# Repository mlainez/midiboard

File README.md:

# MIDI IN/OUT 3V3/5V

A small MIDI interface board: opto-isolated MIDI IN, buffered MIDI OUT, optional hard THRU,
a 3V3/5V slide switch, and on-board footprints for two right-angle DIN-5 jacks.

Board: 46 x 39 mm, 2 layers, all SMD parts on top, 2x M3 mounting holes.

## Ordering at JLCPCB

Everything to upload is in `jlcpcb/`:

| File | Where |
|---|---|
| `midiboard-gerbers.zip` | PCB order: "Add gerber file" |
| `midiboard-BOM.csv` | PCB Assembly step: BOM |
| `midiboard-CPL.csv` | PCB Assembly step: CPL / pick & place |

1. Upload the gerber zip. Defaults are fine (2 layers, 1.6 mm, any colour/finish).
   For "Mark on PCB" choose **Remove Mark** (there is no order-number placeholder on the board).
2. Enable **PCB Assembly**, Economic, **Top side**.
3. Upload BOM and CPL. All 13 placed parts should match automatically:

   | Ref | Value | Package | LCSC | Type |
   |---|---|---|---|---|
   | U1 | H11L1SM optocoupler (onsemi) | SMD DIP-6 | C899473 | extended |
   | U2 | 74LVC1G17W5-7 Schmitt buffer | SOT-23-5 | C151394 | extended |
   | D1 | 1N4148W | SOD-123 | C81598 | basic |
   | SW1 | C&K JS202011JCQN DPDT slide switch | SMD | C221665 | extended |
   | R1, R4, R5 | 220 R | 0603 | C22962 | basic |
   | R2 | 470 R | 0603 | C23179 | basic |
   | R3 | 10 k | 0603 | C25804 | basic |
   | R6 | 33 R | 0805 | C17634 | basic |
   | R7 | 10 R | 0805 | C17415 | basic |
   | C1, C2 | 100 nF X7R | 0603 | C14663 | basic |

4. In the placement preview, check the pin-1 dots: U1 pin 1 is top-left (towards R1/D1), U2 pin 1 is
   top-left (silkscreen triangle). The CPL already applies the KiCad-to-JLCPCB rotation offsets
   (-90 deg for SOT-23-5 and SMD DIP-6).

### Hand-soldered (not in the JLCPCB BOM)

| Ref | Part | Note |
|---|---|---|
| J1, J2 | DIN-5 female, right angle, PCB mount: Legion/Haoyu **DIN-504**, LCSC **C23689428** | Any CUI SDS-50J-footprint jack fits |
| J3 | 1x4 pin header 2.54 mm | MCU side |
| J4 | 1x5 pin header 2.54 mm | Only if you use panel-mount jacks instead of J1/J2 |
| JP1 | 1x2 pin header 2.54 mm + jumper cap | HARD THRU selector |

The DIN jacks can also be added to the JLCPCB order as through-hole assembly if you prefer.

## Pins

**J3 - MCU** (3.3 V or 5 V logic, set SW1 to match)

| Pin | Name | Connect to |
|---|---|---|
| 1 | TX | MCU UART TX (31250 baud) |
| 2 | RX | MCU UART RX |
| 3 | GND | GND |
| 4 | VCC | 3.3 V or 5 V supply, same as the MCU logic level |

**J4 - panel jacks**: `i4`/`i5` to MIDI IN pins 4/5, `o5`/`o2`/`o4` to MIDI OUT pins 5/2/4.
These are wired in parallel with the on-board J1/J2 footprints.

**SW1 3V3 / 5V**: slide towards the jacks (`3V3`) for a 3.3 V MCU, towards the headers (`5V`) for a 5 V MCU.
It only sets the MIDI OUT drive; RX simply swings to VCC. A wrong setting is not harmful: 5 V on the 3V3
setting pushes ~15 mA into the receiver, 3.3 V on the 5V setting gives ~3 mA, which some receivers may not
detect.

**JP1 HARD THRU** (2-pin header, open by default): fit a 2.54 mm jumper cap to echo MIDI IN straight to the OUT jack.
When bridged, leave J3 TX unconnected.

## Circuit notes

- MIDI IN: 220 R + 1N4148W reverse protection into an H11L1 (rated 3-16 V), open-collector output pulled up
  to VCC by 470 R. Accepts 3.3 V and 5 V senders (current loop, ~5-8 mA). IN jack pin 2 is left unconnected and there is no ground copper on the IN side, so the
  input stays galvanically isolated as the MIDI spec requires.
- MIDI OUT: 74LVC1G17 buffer (1.65-5.5 V). 5V position: 220 R from VCC to pin 4 and 220 R in series with
  pin 5 (MIDI 1.0). 3V3 position: SW1 adds 33 R and 10 R in parallel, giving 28.7 R and 9.6 R (CA-033 asks
  for 33 R / 10 R; 33 R is the nearest JLCPCB basic part, ~7 mA instead of ~6.7 mA).
  10 k pull-up on TX keeps the output idle when TX is not driven.

## Verification

`build.sh` runs all of these and stops on failure:

- KiCad ERC on the schematic (0 errors).
- `scripts/check_netlist.py`: the schematic netlist matches `scripts/design.py`.
- KiCad DRC with schematic parity (0 unconnected, 0 parity issues, no clearance errors).
- `scripts/check_gerbers.py`: rasterizes the copper gerbers, joins layers through the drill file's plated
  holes, and derives connectivity from copper alone, then compares it with `design.py` (opens, shorts and
  NC pads). Mutating the expected design makes it fail, so it does detect wiring errors.

Checked by hand against datasheets: H11L1 pinout and inverting output (onsemi), 74LVC1G17 SOT25 pinout
(Diodes Inc), JS202011 contact positions (C&K: slider towards pin 1 closes 1-2 and 4-5), DIN-504 PCB layout
(Legion and Haoyu drawings agree), and the JLCPCB/EasyEDA footprints of C899473, C151394, C81598 and C221665
for the CPL rotations and diode polarity.

`midiboard.kicad_dru` lets through-hole pads have a single thermal spoke per layer: they are plated through
both ground pours, so the connection is solid either way.

## Sources

KiCad project: `midiboard.kicad_pro` / `.kicad_sch` / `.kicad_pcb`, project footprint in `lib/midiboard.pretty`.
`jlcpcb/midiboard-schematic.pdf` is a printable schematic.

Everything is generated from `scripts/design.py` (parts, LCSC numbers, nets):

```
FREEROUTING_JAR=/path/to/freerouting-2.1.0.jar ./build.sh
```

`build.sh` generates the schematic, runs ERC, checks the schematic netlist against `design.py`, places the
board, autoroutes it with Freerouting (headless), adds the ground pours, runs DRC with schematic parity and
writes the JLCPCB files, then checks the gerber copper. It needs KiCad 7 `pcbnew` Python, `kiutils`, numpy,
scipy, pillow, gerbv, Java 21 and a KiCad >= 8 `kicad-cli` (defaults to the KiCad Flatpak).

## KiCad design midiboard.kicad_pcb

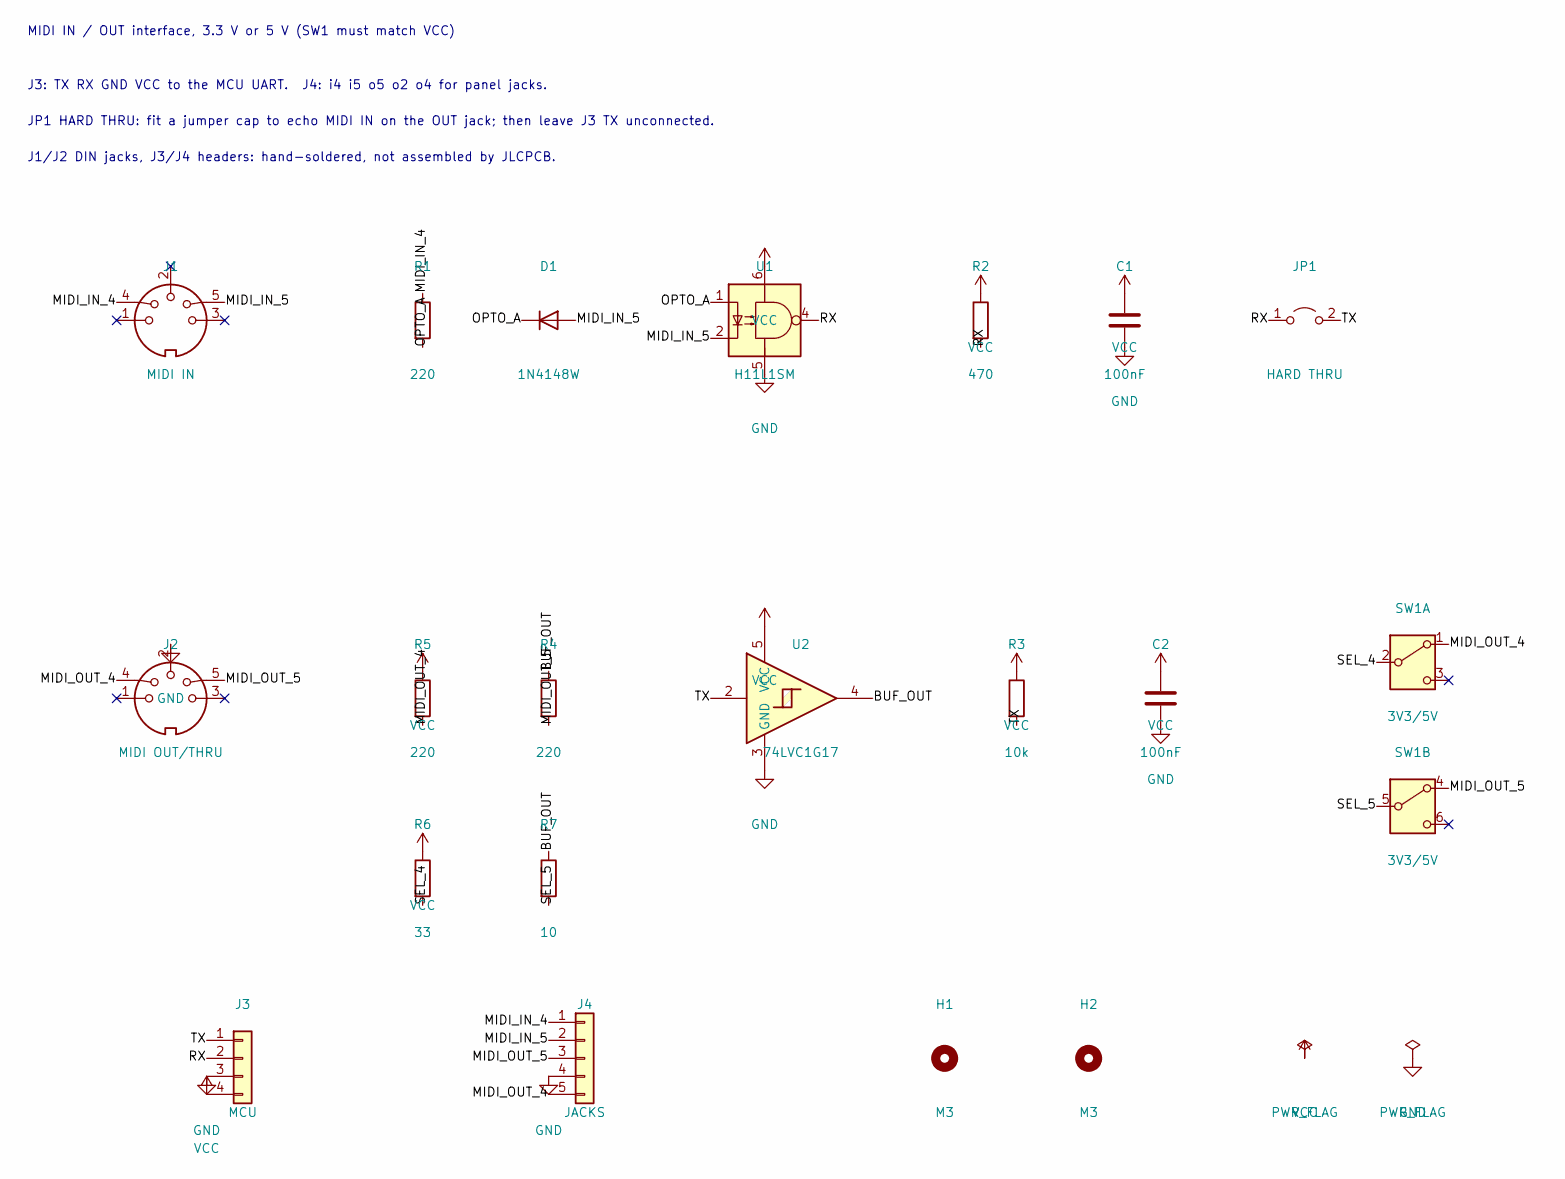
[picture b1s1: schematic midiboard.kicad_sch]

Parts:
C1, C2: 100nF; C_0603_1608Metric; MPN CC0603KRX7R9BB104; LCSC C14663
D1: 1N4148W; D_SOD-123; MPN 1N4148W; LCSC C81598
H1, H2: M3; MountingHole_3.2mm_M3
J1: MIDI IN; DIN-5_Female_Horizontal_DIN-504; MPN Legion DIN-504 (LCSC C23689428)
J2: MIDI OUT/THRU; DIN-5_Female_Horizontal_DIN-504; MPN Legion DIN-504 (LCSC C23689428)
J3: MCU; PinHeader_1x04_P2.54mm_Vertical; MPN 2.54mm pin header 1x4
J4: JACKS; PinHeader_1x05_P2.54mm_Vertical; MPN 2.54mm pin header 1x5
JP1: HARD THRU; PinHeader_1x02_P2.54mm_Vertical; MPN 2.54mm pin header 1x2 + jumper cap
R1, R4, R5: 220; R_0603_1608Metric; MPN 0603WAF2200T5E; LCSC C22962
R2: 470; R_0603_1608Metric; MPN 0603WAF4700T5E; LCSC C23179
R3: 10k; R_0603_1608Metric; MPN 0603WAF1002T5E; LCSC C25804
R6: 33; R_0805_2012Metric; MPN 0805W8F330JT5E; LCSC C17634
R7: 10; R_0805_2012Metric; MPN 0805W8F100JT5E; LCSC C17415
SW1: 3V3/5V; SW_DPDT_CK_JS202011JCQN; MPN C&K JS202011JCQN; LCSC C221665
U1: H11L1SM; SMDIP-6_W9.53mm; MPN onsemi H11L1SM; LCSC C899473
U2: 74LVC1G17; SOT-23-5; MPN Diodes 74LVC1G17W5-7; LCSC C151394

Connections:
/BUF_OUT: R4.1, R7.1, U2.4
/MIDI_IN_4: J1.4, J4.1, R1.1
/MIDI_IN_5: D1.2 (A), J1.5, J4.2, U1.2
/MIDI_OUT_4: J2.4, J4.5, R5.2, SW1.1 (A)
/MIDI_OUT_5: J2.5, J4.3, R4.2, SW1.4 (A)
/OPTO_A: D1.1 (K), R1.2, U1.1
/RX: J3.2, JP1.1 (A), R2.2, U1.4
/SEL_4: R6.2, SW1.2 (B)
/SEL_5: R7.2, SW1.5 (B)
/TX: J3.1, JP1.2 (B), R3.2, U2.2
GND: C1.2, C2.2, J2.2, J3.3, J4.4, U1.5, U2.3 (GND)
VCC: C1.1, C2.1, J3.4, R2.1, R3.1, R5.1, R6.1, U1.6, U2.5 (VCC)

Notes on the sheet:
MIDI IN / OUT interface, 3.3 V or 5 V (SW1 must match VCC)
J3: TX RX GND VCC to the MCU UART. J4: i4 i5 o5 o2 o4 for panel jacks.
JP1 HARD THRU: fit a jumper cap to echo MIDI IN on the OUT jack; then leave J3 TX unconnected.
J1/J2 DIN jacks, J3/J4 headers: hand-soldered, not assembled by JLCPCB.

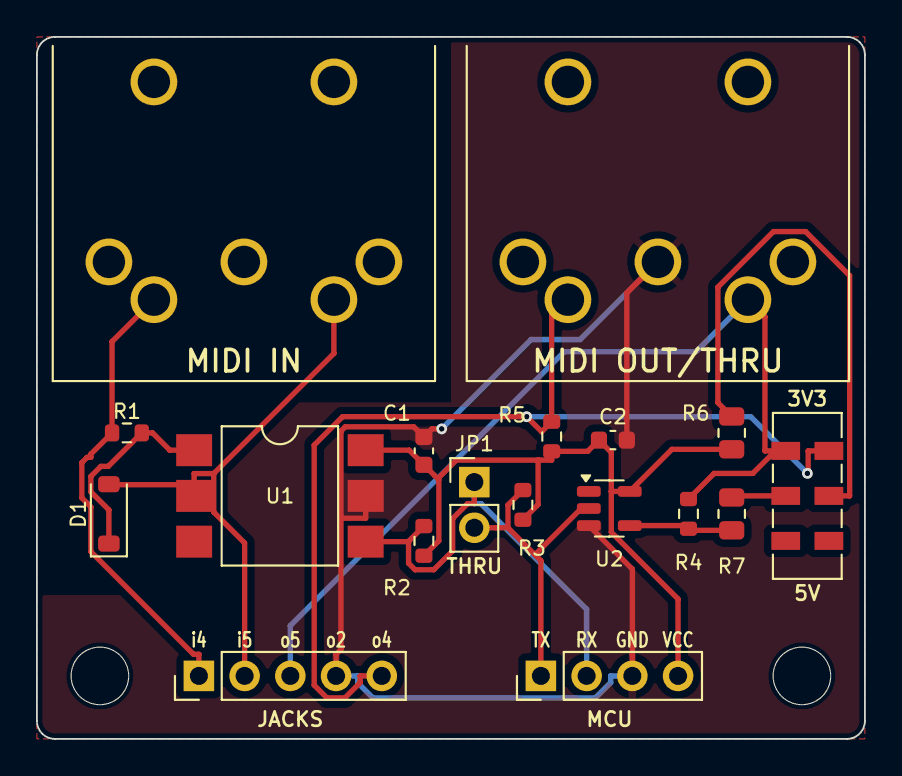
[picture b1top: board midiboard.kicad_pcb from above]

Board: 2 copper layers, 46.0 x 39.0 mm, 20 parts (0 on the bottom side), 12 nets.

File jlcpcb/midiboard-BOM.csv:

Comment,Designator,Footprint,LCSC Part #
100nF,"C1,C2",C_0603_1608Metric,C14663
1N4148W,D1,D_SOD-123,C81598
220,"R1,R4,R5",R_0603_1608Metric,C22962
470,R2,R_0603_1608Metric,C23179
10k,R3,R_0603_1608Metric,C25804
33,R6,R_0805_2012Metric,C17634
10,R7,R_0805_2012Metric,C17415
3V3/5V,SW1,SW_DPDT_CK_JS202011JCQN,C221665
H11L1SM,U1,SMDIP-6_W9.53mm,C899473
74LVC1G17,U2,SOT-23-5,C151394

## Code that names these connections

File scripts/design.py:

"""Single source of truth for the MIDI 3V3/5V board: parts, footprints, LCSC numbers and nets.

Both the schematic generator and the PCB generator import this module, so the
schematic and the layout can never disagree on connectivity.
"""

PROJECT = "midiboard"

# Footprint rotation offsets (deg) between KiCad and JLCPCB placement conventions.
JLC_ROTATION = {
    "Package_TO_SOT_SMD:SOT-23-5": -90,
    "Package_DIP:SMDIP-6_W9.53mm": -90,
}

# Each part: reference -> dict.
#   sym:   KiCad library symbol
#   fp:    footprint
#   lcsc:  LCSC/JLCPCB part number, or None when the part is not assembled by JLCPCB
#   pins:  pin number -> net name (None = not connected)
#   bom:   False for board features (mounting holes) that are not bill-of-materials items
PARTS = {
    "J1": dict(sym="Connector:DIN-5_180degree", value="MIDI IN",
               fp="midiboard:DIN-5_Female_Horizontal_DIN-504", lcsc=None,
               mpn="Legion DIN-504 (LCSC C23689428)",
               pins={"1": None, "2": None, "3": None, "4": "MIDI_IN_4", "5": "MIDI_IN_5"}),
    "J2": dict(sym="Connector:DIN-5_180degree", value="MIDI OUT/THRU",
               fp="midiboard:DIN-5_Female_Horizontal_DIN-504", lcsc=None,
               mpn="Legion DIN-504 (LCSC C23689428)",
               pins={"1": None, "2": "GND", "3": None, "4": "MIDI_OUT_4", "5": "MIDI_OUT_5"}),
    "R1": dict(sym="Device:R", value="220", fp="Resistor_SMD:R_0603_1608Metric", lcsc="C22962",
               mpn="0603WAF2200T5E", pins={"1": "MIDI_IN_4", "2": "OPTO_A"}),
    "D1": dict(sym="Device:D", value="1N4148W", fp="Diode_SMD:D_SOD-123", lcsc="C81598",
               mpn="1N4148W", pins={"1": "OPTO_A", "2": "MIDI_IN_5"}),
    "U1": dict(sym="Isolator:H11L1", value="H11L1SM", fp="Package_DIP:SMDIP-6_W9.53mm", lcsc="C899473",
               mpn="onsemi H11L1SM",
               pins={"1": "OPTO_A", "2": "MIDI_IN_5", "3": None, "4": "RX", "5": "GND", "6": "VCC"}),
    "R2": dict(sym="Device:R", value="470", fp="Resistor_SMD:R_0603_1608Metric", lcsc="C23179",
               mpn="0603WAF4700T5E", pins={"1": "VCC", "2": "RX"}),
    "C1": dict(sym="Device:C", value="100nF", fp="Capacitor_SMD:C_0603_1608Metric", lcsc="C14663",
               mpn="CC0603KRX7R9BB104", pins={"1": "VCC", "2": "GND"}),
    # 2-pin header for a removable 2.54 mm jumper cap: fitted = hard THRU (RX drives the OUT buffer).
    "JP1": dict(sym="Jumper:Jumper_2_Open", value="HARD THRU",
                fp="Connector_PinHeader_2.54mm:PinHeader_1x02_P2.54mm_Vertical", lcsc=None,
                mpn="2.54mm pin header 1x2 + jumper cap", pins={"1": "RX", "2": "TX"}),
    "R3": dict(sym="Device:R", value="10k", fp="Resistor_SMD:R_0603_1608Metric", lcsc="C25804",
               mpn="0603WAF1002T5E", pins={"1": "VCC", "2": "TX"}),
    "U2": dict(sym="74xGxx:74LVC1G17", value="74LVC1G17", fp="Package_TO_SOT_SMD:SOT-23-5", lcsc="C151394",
               mpn="Diodes 74LVC1G17W5-7",
               pins={"1": None, "2": "TX", "3": "GND", "4": "BUF_OUT", "5": "VCC"}),
    "C2": dict(sym="Device:C", value="100nF", fp="Capacitor_SMD:C_0603_1608Metric", lcsc="C14663",
               mpn="CC0603KRX7R9BB104", pins={"1": "VCC", "2": "GND"}),
    # MIDI OUT source resistors: 220R each for 5 V (MIDI 1.0). In the 3V3 position SW1 puts R6/R7 in
    # parallel: 220R || 33R = 28.7R on pin 4 and 220R || 10R = 9.6R on pin 5 (CA-033: 33R / 10R).
    "R4": dict(sym="Device:R", value="220", fp="Resistor_SMD:R_0603_1608Metric", lcsc="C22962",
               mpn="0603WAF2200T5E", pins={"1": "BUF_OUT", "2": "MIDI_OUT_5"}),
    "R5": dict(sym="Device:R", value="220", fp="Resistor_SMD:R_0603_1608Metric", lcsc="C22962",
               mpn="0603WAF2200T5E", pins={"1": "VCC", "2": "MIDI_OUT_4"}),
    "R6": dict(sym="Device:R", value="33", fp="Resistor_SMD:R_0805_2012Metric", lcsc="C17634",
               mpn="0805W8F330JT5E", pins={"1": "VCC", "2": "SEL_4"}),
    "R7": dict(sym="Device:R", value="10", fp="Resistor_SMD:R_0805_2012Metric", lcsc="C17415",
               mpn="0805W8F100JT5E", pins={"1": "BUF_OUT", "2": "SEL_5"}),
    # Slider towards pins 1/4 = 3V3 (1-2 and 4-5 closed); towards pins 3/6 = 5V (R6/R7 out of circuit).
    "SW1": dict(sym="Switch:SW_DPDT_x2", value="3V3/5V", fp="Button_Switch_SMD:SW_DPDT_CK_JS202011JCQN",
                lcsc="C221665", mpn="C&K JS202011JCQN",
                pins={"1": "MIDI_OUT_4", "2": "SEL_4", "3": None, "4": "MIDI_OUT_5", "5": "SEL_5", "6": None}),
    "J3": dict(sym="Connector_Generic:Conn_01x04", value="MCU",
               fp="Connector_PinHeader_2.54mm:PinHeader_1x04_P2.54mm_Vertical", lcsc=None,
               mpn="2.54mm pin header 1x4",
               pins={"1": "TX", "2": "RX", "3": "GND", "4": "VCC"}),
    "J4": dict(sym="Connector_Generic:Conn_01x05", value="JACKS",
               fp="Connector_PinHeader_2.54mm:PinHeader_1x05_P2.54mm_Vertical", lcsc=None,
               mpn="2.54mm pin header 1x5",
               pins={"1": "MIDI_IN_4", "2": "MIDI_IN_5", "3": "MIDI_OUT_5", "4": "GND", "5": "MIDI_OUT_4"}),
    "H1": dict(sym="Mechanical:MountingHole", value="M3", fp="MountingHole:MountingHole_3.2mm_M3",
               lcsc=None, mpn="", bom=False, pins={}),
    "H2": dict(sym="Mechanical:MountingHole", value="M3", fp="MountingHole:MountingHole_3.2mm_M3",
               lcsc=None, mpn="", bom=False, pins={}),
}

POWER_NETS = ("VCC", "GND")
